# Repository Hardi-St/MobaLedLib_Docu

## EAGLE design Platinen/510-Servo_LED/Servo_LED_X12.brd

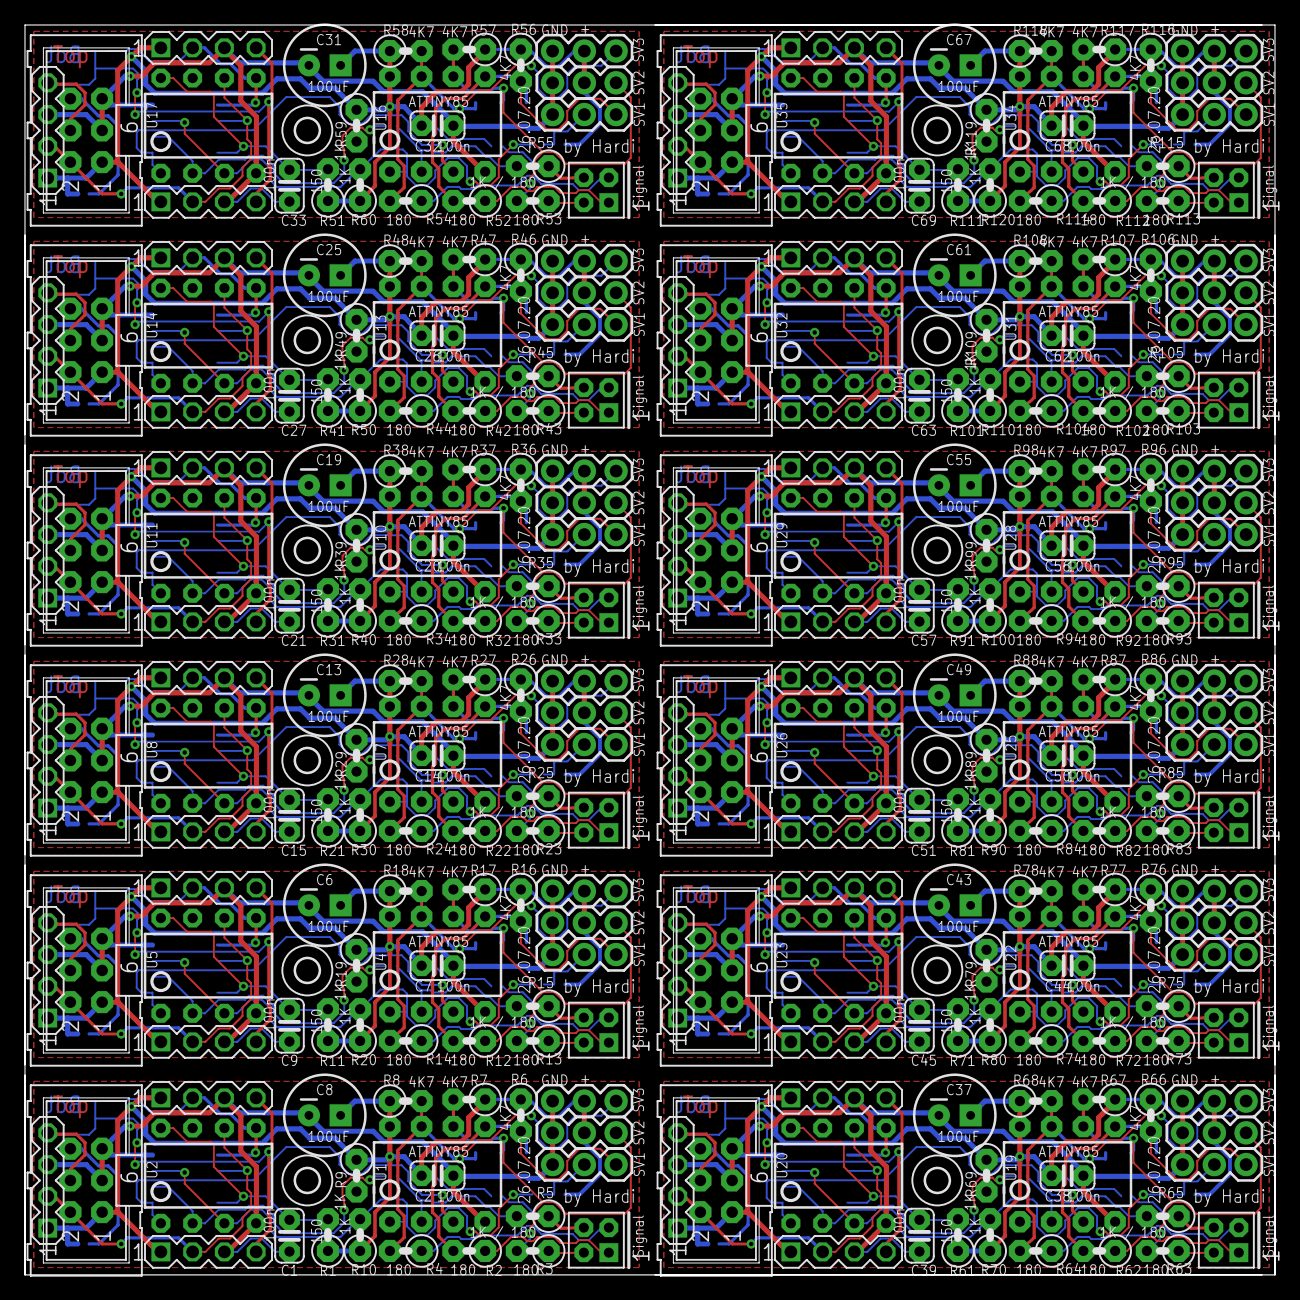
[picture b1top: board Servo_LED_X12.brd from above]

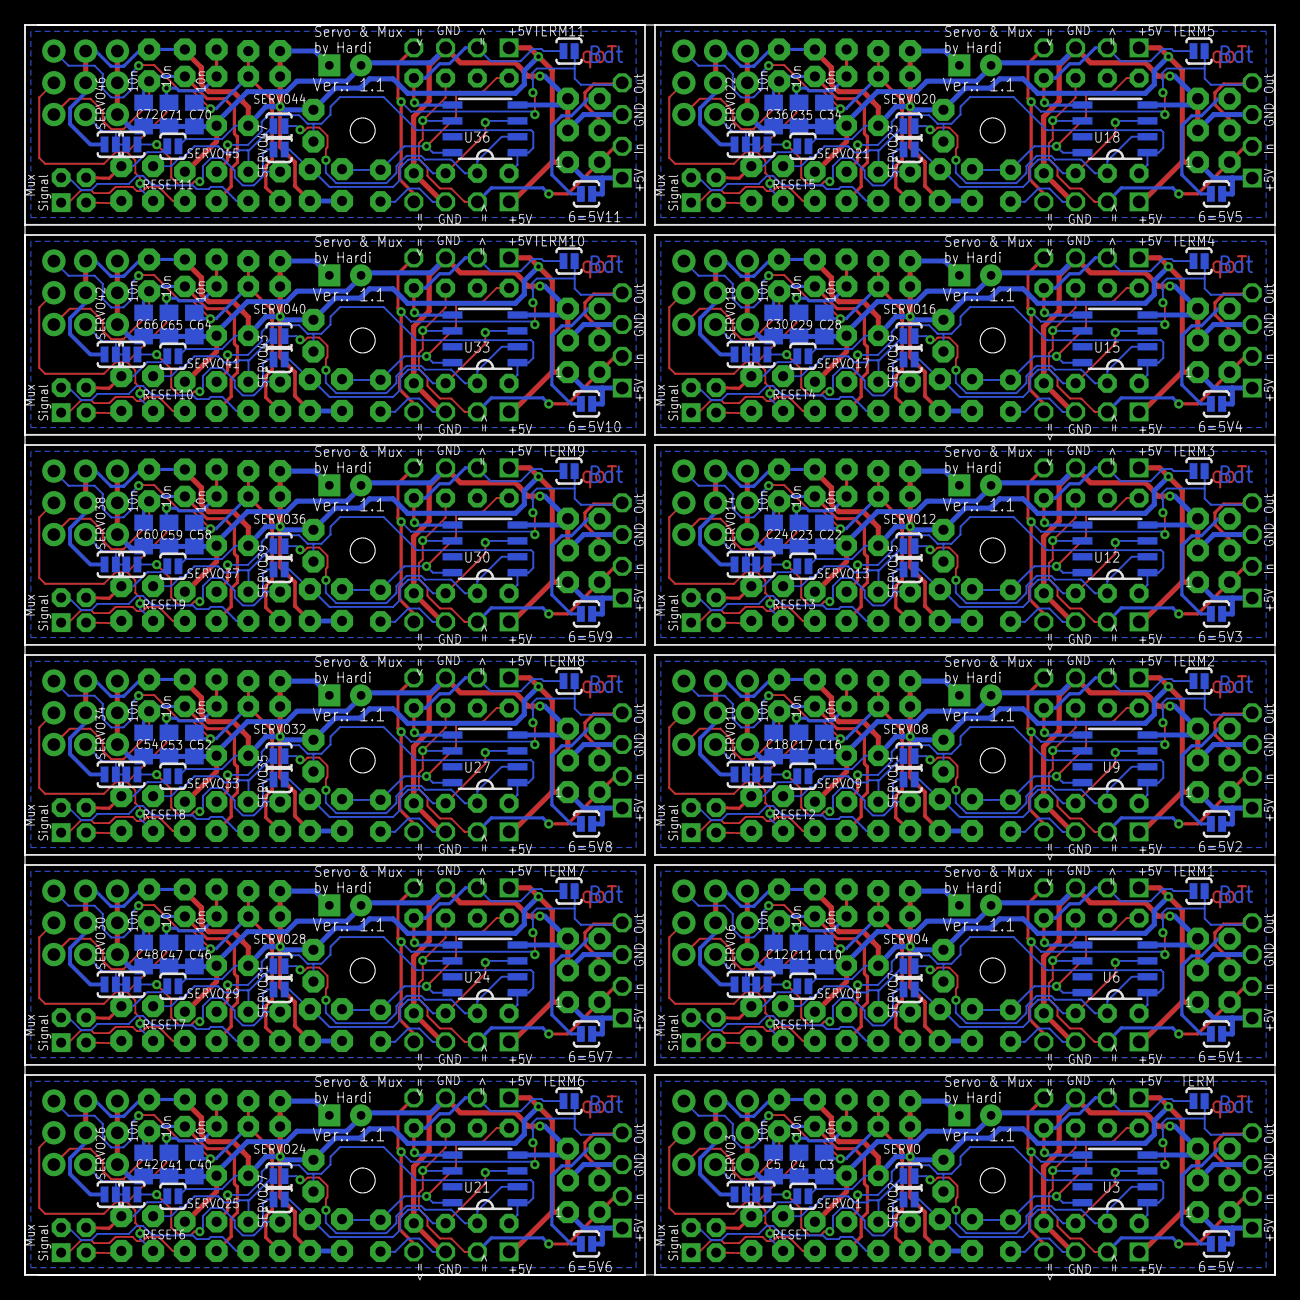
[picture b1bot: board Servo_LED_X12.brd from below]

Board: 2 copper layers, 100.0 x 100.0 mm, 420 parts (132 on the bottom side), 240 nets.

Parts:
6=5V, 6=5V1, 6=5V2, 6=5V3, 6=5V4, 6=5V5, 6=5V6, 6=5V7, 6=5V8, 6=5V9, 6=5V10, 6=5V11: SOLDERJUMPERNO; SJ_2S-NO
C1, C2, C7, C9, C14, C15, C20, C21, C26, C27, C32, C33, C38, C39, C44, C45, C50, C51, C56, C57, C62, C63, C68, C69: 100n; C025-024X044
C3, C4, C5, C10, C11, C12, C16, C17, C18, C22, C23, C24, C28, C29, C30, C34, C35, C36, C40, C41, C42, C46, C47, C48, C52, C53, C54, C58, C59, C60, C64, C65, C66, C70, C71, C72: 10n; C0805
C6, C8, C13, C19, C25, C31, C37, C43, C49, C55, C61, C67: 100uF; SPARKFUN-CAPACITORS_CPOL-RADIAL-100UF-25V
H1, H2, H3, H4, H5, H6, H7, H8, H9, H10, H11, H12: MOUNT-HOLE2.0; 2,0
J1, J4, J7, J10, J13, J16, J19, J22, J25, J28, J31, J34: SV1; 1X03
J2, J5, J8, J11, J14, J17, J20, J23, J26, J29, J32, J35: SV2; 1X03
J3, J6, J9, J12, J15, J18, J21, J24, J27, J30, J33, J36: SV3; 1X03
O1, O2, O3, O4, O5, O6, O7, O8, O9, O10, O11, O12: ML6
R1, R11, R21, R31, R41, R51, R61, R71, R81, R91, R101, R111: 150; RCL_0207/2V
R2, R3, R4, R12, R13, R14, R22, R23, R24, R32, R33, R34, R42, R43, R44, R52, R53, R54, R62, R63, R64, R72, R73, R74, R82, R83, R84, R92, R93, R94, R102, R103, R104, R112, R113, R114: 180; RCL_0207/2V
R5, R15, R25, R35, R45, R55, R65, R75, R85, R95, R105, R115: 1K / 180; RCL_0207/2V
R6, R7, R8, R16, R17, R18, R26, R27, R28, R36, R37, R38, R46, R47, R48, R56, R57, R58, R66, R67, R68, R76, R77, R78, R86, R87, R88, R96, R97, R98, R106, R107, R108, R116, R117, R118: 4K7; RCL_0207/2V
R9, R10, R19, R20, R29, R30, R39, R40, R49, R50, R59, R60, R69, R70, R79, R80, R89, R90, R99, R100, R109, R110, R119, R120: 1K; RCL_0207/2V
RESET, RESET1, RESET2, RESET3, RESET4, RESET5, RESET6, RESET7, RESET8, RESET9, RESET10, RESET11: SOLDERJUMPERNO; SJ_2S-NO
SERVO, SERVO1, SERVO2, SERVO3, SERVO4, SERVO5, SERVO6, SERVO7, SERVO8, SERVO9, SERVO10, SERVO11, SERVO12, SERVO13, SERVO14, SERVO15, SERVO16, SERVO17, SERVO18, SERVO19, SERVO20, SERVO21, SERVO22, SERVO23, SERVO24, SERVO25, SERVO26, SERVO27, SERVO28, SERVO29, SERVO30, SERVO31, SERVO32, SERVO33, SERVO34, SERVO35, SERVO36, SERVO37, SERVO38, SERVO39, SERVO40, SERVO41, SERVO42, SERVO43, SERVO44, SERVO45, SERVO46, SERVO47: SOLDERJUMPERNO; SJ_2S-NO
SV1, SV8, SV12, SV16, SV20, SV24, SV28, SV32, SV36, SV40, SV44, SV48: MUX-SIGNAL
SV2, SV3, SV4, SV5, SV6, SV7, SV9, SV10, SV11, SV13, SV14, SV15, SV17, SV18, SV19, SV21, SV22, SV23, SV25, SV26, SV27, SV29, SV30, SV31, SV33, SV34, SV35, SV37, SV38, SV39, SV41, SV42, SV43, SV45, SV46, SV47: MA04-1
TERM, TERM1, TERM2, TERM3, TERM4, TERM5, TERM6, TERM7, TERM8, TERM9, TERM10, TERM11: SOLDERJUMPERNO; SJ_2S-NO
U1, U4, U7, U10, U13, U16, U19, U22, U25, U28, U31, U34: ATTINY85; DIP08
U2, U5, U8, U11, U14, U17, U20, U23, U26, U29, U32, U35: TINY45-20-DIP; S3PO_MODUL_WS2811_SOUND_MP3-TF-16P_WS2811_AND_ATTINY_WS2811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
U3, U6, U9, U12, U15, U18, U21, U24, U27, U30, U33, U36: WS2811 SOT-8; SOP8

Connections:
+5V: 6=5V.2, C2.1, C8.1, J2.2, J3.2, O1.1, R1.1, R6.1, R7.1, R8.1, R9.1, R10.1, SERVO1.2, SERVO3.2, SV3.1, SV4.1, SV5.1, U1.8
+5V1: 6=5V1.2, C6.1, C7.1, J5.2, J6.2, O2.1, R11.1, R16.1, R17.1, R18.1, R19.1, R20.1, SERVO5.2, SERVO6.2, SV2.1, SV6.1, SV7.1, U4.8
+5V2: 6=5V2.2, C13.1, C14.1, J8.2, J9.2, O3.1, R21.1, R26.1, R27.1, R28.1, R29.1, R30.1, SERVO9.2, SERVO10.2, SV9.1, SV10.1, SV11.1, U7.8
+5V3: 6=5V3.2, C19.1, C20.1, J11.2, J12.2, O4.1, R31.1, R36.1, R37.1, R38.1, R39.1, R40.1, SERVO13.2, SERVO14.2, SV13.1, SV14.1, SV15.1, U10.8
+5V4: 6=5V4.2, C25.1, C26.1, J14.2, J15.2, O5.1, R41.1, R46.1, R47.1, R48.1, R49.1, R50.1, SERVO17.2, SERVO18.2, SV17.1, SV18.1, SV19.1, U13.8
+5V5: 6=5V5.2, C31.1, C32.1, J17.2, J18.2, O6.1, R51.1, R56.1, R57.1, R58.1, R59.1, R60.1, SERVO21.2, SERVO22.2, SV21.1, SV22.1, SV23.1, U16.8
+5V6: 6=5V6.2, C37.1, C38.1, J20.2, J21.2, O7.1, R61.1, R66.1, R67.1, R68.1, R69.1, R70.1, SERVO25.2, SERVO26.2, SV25.1, SV26.1, SV27.1, U19.8
+5V7: 6=5V7.2, C43.1, C44.1, J23.2, J24.2, O8.1, R71.1, R76.1, R77.1, R78.1, R79.1, R80.1, SERVO29.2, SERVO30.2, SV29.1, SV30.1, SV31.1, U22.8
+5V8: 6=5V8.2, C49.1, C50.1, J26.2, J27.2, O9.1, R81.1, R86.1, R87.1, R88.1, R89.1, R90.1, SERVO33.2, SERVO34.2, SV33.1, SV34.1, SV35.1, U25.8
+5V9: 6=5V9.2, C55.1, C56.1, J29.2, J30.2, O10.1, R91.1, R96.1, R97.1, R98.1, R99.1, R100.1, SERVO37.2, SERVO38.2, SV37.1, SV38.1, SV39.1, U28.8
+5V10: 6=5V10.2, C61.1, C62.1, J32.2, J33.2, O11.1, R101.1, R106.1, R107.1, R108.1, R109.1, R110.1, SERVO41.2, SERVO42.2, SV41.1, SV42.1, SV43.1, U31.8
+5V11: 6=5V11.2, C67.1, C68.1, J35.2, J36.2, O12.1, R111.1, R116.1, R117.1, R118.1, R119.1, R120.1, SERVO45.2, SERVO46.2, SV45.1, SV46.1, SV47.1, U34.8
GND: C1.2, C2.2, C3.2, C4.2, C5.2, C8.2, J1.3, J2.3, J3.3, O1.3, O1.5, SV3.3, SV4.3, SV5.3, U1.4, U2.4, U3.4
GND1: C6.2, C7.2, C9.2, C10.2, C11.2, C12.2, J4.3, J5.3, J6.3, O2.3, O2.5, SV2.3, SV6.3, SV7.3, U4.4, U5.4, U6.4
GND2: C13.2, C14.2, C15.2, C16.2, C17.2, C18.2, J7.3, J8.3, J9.3, O3.3, O3.5, SV9.3, SV10.3, SV11.3, U7.4, U8.4, U9.4
GND3: C19.2, C20.2, C21.2, C22.2, C23.2, C24.2, J10.3, J11.3, J12.3, O4.3, O4.5, SV13.3, SV14.3, SV15.3, U10.4, U11.4, U12.4
GND4: C25.2, C26.2, C27.2, C28.2, C29.2, C30.2, J13.3, J14.3, J15.3, O5.3, O5.5, SV17.3, SV18.3, SV19.3, U13.4, U14.4, U15.4
GND5: C31.2, C32.2, C33.2, C34.2, C35.2, C36.2, J16.3, J17.3, J18.3, O6.3, O6.5, SV21.3, SV22.3, SV23.3, U16.4, U17.4, U18.4
GND6: C37.2, C38.2, C39.2, C40.2, C41.2, C42.2, J19.3, J20.3, J21.3, O7.3, O7.5, SV25.3, SV26.3, SV27.3, U19.4, U20.4, U21.4
GND7: C43.2, C44.2, C45.2, C46.2, C47.2, C48.2, J22.3, J23.3, J24.3, O8.3, O8.5, SV29.3, SV30.3, SV31.3, U22.4, U23.4, U24.4
GND8: C49.2, C50.2, C51.2, C52.2, C53.2, C54.2, J25.3, J26.3, J27.3, O9.3, O9.5, SV33.3, SV34.3, SV35.3, U25.4, U26.4, U27.4
GND9: C55.2, C56.2, C57.2, C58.2, C59.2, C60.2, J28.3, J29.3, J30.3, O10.3, O10.5, SV37.3, SV38.3, SV39.3, U28.4, U29.4, U30.4
GND10: C61.2, C62.2, C63.2, C64.2, C65.2, C66.2, J31.3, J32.3, J33.3, O11.3, O11.5, SV41.3, SV42.3, SV43.3, U31.4, U32.4, U33.4
GND11: C67.2, C68.2, C69.2, C70.2, C71.2, C72.2, J34.3, J35.3, J36.3, O12.3, O12.5, SV45.3, SV46.3, SV47.3, U34.4, U35.4, U36.4
unnamed: O1.2, SV4.2, SV5.2, U2.6, U3.6
unnamed: SV3.2, TERM.2, U2.5, U3.5
unnamed: O1.4, SV3.4, SV4.4, SV5.4, TERM.1
unnamed: C1.1, R1.2, U2.8, U3.8
unnamed: R2.1, SV1.1
unnamed: 6=5V.1, O1.6
unnamed: R9.2, U1.3, U2.1, U3.1
unnamed: R5.2, SERVO.2, U1.2
unnamed: C4.1, J2.1, R3.2, R7.2, U1.6
unnamed: R4.1, SV1.3
unnamed: R3.1, SV1.2
unnamed: R5.1, SERVO1.1, SV1.4
unnamed: SERVO.1, U2.2, U3.2
unnamed: C3.1, J3.1, R4.2, R8.2, U1.7
unnamed: RESET.1, SERVO2.2, U1.1
unnamed: C5.1, J1.1, R2.2, R6.2, U1.5
unnamed: J1.2, RESET.2, SERVO3.1
unnamed: R10.2, SERVO2.1, U2.3, U3.3
unnamed: O2.2, SV6.2, SV7.2, U5.6, U6.6
unnamed: SV2.2, TERM1.2, U5.5, U6.5
unnamed: O2.4, SV2.4, SV6.4, SV7.4, TERM1.1
unnamed: C9.1, R11.2, U5.8, U6.8
unnamed: R19.2, U4.3, U5.1, U6.1
unnamed: C11.1, J5.1, R13.2, R17.2, U4.6
unnamed: C10.1, J6.1, R14.2, R18.2, U4.7
unnamed: C12.1, J4.1, R12.2, R16.2, U4.5
unnamed: RESET1.1, SERVO7.2, U4.1
unnamed: R12.1, SV8.1
unnamed: R14.1, SV8.3
unnamed: R13.1, SV8.2
unnamed: R15.1, SERVO5.1, SV8.4
unnamed: R15.2, SERVO4.2, U4.2
unnamed: SERVO4.1, U5.2, U6.2
unnamed: 6=5V1.1, O2.6
unnamed: J4.2, RESET1.2, SERVO6.1
unnamed: R20.2, SERVO7.1, U5.3, U6.3
unnamed: O3.2, SV10.2, SV11.2, U8.6, U9.6
unnamed: SV9.2, TERM2.2, U8.5, U9.5
unnamed: O3.4, SV9.4, SV10.4, SV11.4, TERM2.1
unnamed: C15.1, R21.2, U8.8, U9.8
unnamed: R29.2, U7.3, U8.1, U9.1
unnamed: C17.1, J8.1, R23.2, R27.2, U7.6
unnamed: C16.1, J9.1, R24.2, R28.2, U7.7
unnamed: C18.1, J7.1, R22.2, R26.2, U7.5
unnamed: RESET2.1, SERVO11.2, U7.1
unnamed: R22.1, SV12.1
unnamed: R24.1, SV12.3
unnamed: R23.1, SV12.2
unnamed: R25.1, SERVO9.1, SV12.4
unnamed: R25.2, SERVO8.2, U7.2
unnamed: SERVO8.1, U8.2, U9.2
unnamed: 6=5V2.1, O3.6
unnamed: J7.2, RESET2.2, SERVO10.1
unnamed: R30.2, SERVO11.1, U8.3, U9.3
unnamed: O4.2, SV14.2, SV15.2, U11.6, U12.6
unnamed: SV13.2, TERM3.2, U11.5, U12.5
unnamed: O4.4, SV13.4, SV14.4, SV15.4, TERM3.1
unnamed: C21.1, R31.2, U11.8, U12.8
unnamed: R39.2, U10.3, U11.1, U12.1
unnamed: C23.1, J11.1, R33.2, R37.2, U10.6
unnamed: C22.1, J12.1, R34.2, R38.2, U10.7
unnamed: C24.1, J10.1, R32.2, R36.2, U10.5
unnamed: RESET3.1, SERVO15.2, U10.1
unnamed: R32.1, SV16.1
unnamed: R34.1, SV16.3
unnamed: R33.1, SV16.2
unnamed: R35.1, SERVO13.1, SV16.4
unnamed: R35.2, SERVO12.2, U10.2
unnamed: SERVO12.1, U11.2, U12.2
unnamed: 6=5V3.1, O4.6
unnamed: J10.2, RESET3.2, SERVO14.1
unnamed: R40.2, SERVO15.1, U11.3, U12.3
unnamed: O5.2, SV18.2, SV19.2, U14.6, U15.6
unnamed: SV17.2, TERM4.2, U14.5, U15.5
unnamed: O5.4, SV17.4, SV18.4, SV19.4, TERM4.1
unnamed: C27.1, R41.2, U14.8, U15.8
unnamed: R49.2, U13.3, U14.1, U15.1
unnamed: C29.1, J14.1, R43.2, R47.2, U13.6
unnamed: C28.1, J15.1, R44.2, R48.2, U13.7
unnamed: C30.1, J13.1, R42.2, R46.2, U13.5
unnamed: RESET4.1, SERVO19.2, U13.1
unnamed: R42.1, SV20.1
unnamed: R44.1, SV20.3
unnamed: R43.1, SV20.2
unnamed: R45.1, SERVO17.1, SV20.4
unnamed: R45.2, SERVO16.2, U13.2
unnamed: SERVO16.1, U14.2, U15.2
unnamed: 6=5V4.1, O5.6
unnamed: J13.2, RESET4.2, SERVO18.1
unnamed: R50.2, SERVO19.1, U14.3, U15.3
unnamed: O6.2, SV22.2, SV23.2, U17.6, U18.6
unnamed: SV21.2, TERM5.2, U17.5, U18.5
unnamed: O6.4, SV21.4, SV22.4, SV23.4, TERM5.1
unnamed: C33.1, R51.2, U17.8, U18.8
unnamed: R59.2, U16.3, U17.1, U18.1
unnamed: C35.1, J17.1, R53.2, R57.2, U16.6
unnamed: C34.1, J18.1, R54.2, R58.2, U16.7
unnamed: C36.1, J16.1, R52.2, R56.2, U16.5
unnamed: RESET5.1, SERVO23.2, U16.1
unnamed: R52.1, SV24.1
unnamed: R54.1, SV24.3
unnamed: R53.1, SV24.2
unnamed: R55.1, SERVO21.1, SV24.4
unnamed: R55.2, SERVO20.2, U16.2
unnamed: SERVO20.1, U17.2, U18.2
unnamed: 6=5V5.1, O6.6
unnamed: J16.2, RESET5.2, SERVO22.1
unnamed: R60.2, SERVO23.1, U17.3, U18.3
unnamed: O7.2, SV26.2, SV27.2, U20.6, U21.6
unnamed: SV25.2, TERM6.2, U20.5, U21.5
unnamed: O7.4, SV25.4, SV26.4, SV27.4, TERM6.1
unnamed: C39.1, R61.2, U20.8, U21.8
unnamed: R69.2, U19.3, U20.1, U21.1
unnamed: C41.1, J20.1, R63.2, R67.2, U19.6
unnamed: C40.1, J21.1, R64.2, R68.2, U19.7
unnamed: C42.1, J19.1, R62.2, R66.2, U19.5
unnamed: RESET6.1, SERVO27.2, U19.1
unnamed: R62.1, SV28.1
unnamed: R64.1, SV28.3
unnamed: R63.1, SV28.2
unnamed: R65.1, SERVO25.1, SV28.4
unnamed: R65.2, SERVO24.2, U19.2
unnamed: SERVO24.1, U20.2, U21.2
unnamed: 6=5V6.1, O7.6
unnamed: J19.2, RESET6.2, SERVO26.1
unnamed: R70.2, SERVO27.1, U20.3, U21.3
unnamed: O8.2, SV30.2, SV31.2, U23.6, U24.6
unnamed: SV29.2, TERM7.2, U23.5, U24.5
unnamed: O8.4, SV29.4, SV30.4, SV31.4, TERM7.1
unnamed: C45.1, R71.2, U23.8, U24.8
unnamed: R79.2, U22.3, U23.1, U24.1
unnamed: C47.1, J23.1, R73.2, R77.2, U22.6
unnamed: C46.1, J24.1, R74.2, R78.2, U22.7
unnamed: C48.1, J22.1, R72.2, R76.2, U22.5
unnamed: RESET7.1, SERVO31.2, U22.1
unnamed: R72.1, SV32.1
unnamed: R74.1, SV32.3
unnamed: R73.1, SV32.2
unnamed: R75.1, SERVO29.1, SV32.4
unnamed: R75.2, SERVO28.2, U22.2
unnamed: SERVO28.1, U23.2, U24.2
unnamed: 6=5V7.1, O8.6
unnamed: J22.2, RESET7.2, SERVO30.1
unnamed: R80.2, SERVO31.1, U23.3, U24.3
unnamed: O9.2, SV34.2, SV35.2, U26.6, U27.6
unnamed: SV33.2, TERM8.2, U26.5, U27.5
unnamed: O9.4, SV33.4, SV34.4, SV35.4, TERM8.1
unnamed: C51.1, R81.2, U26.8, U27.8
unnamed: R89.2, U25.3, U26.1, U27.1
unnamed: C53.1, J26.1, R83.2, R87.2, U25.6
unnamed: C52.1, J27.1, R84.2, R88.2, U25.7
unnamed: C54.1, J25.1, R82.2, R86.2, U25.5
unnamed: RESET8.1, SERVO35.2, U25.1
unnamed: R82.1, SV36.1
unnamed: R84.1, SV36.3
unnamed: R83.1, SV36.2
unnamed: R85.1, SERVO33.1, SV36.4
unnamed: R85.2, SERVO32.2, U25.2
unnamed: SERVO32.1, U26.2, U27.2
unnamed: 6=5V8.1, O9.6
unnamed: J25.2, RESET8.2, SERVO34.1
unnamed: R90.2, SERVO35.1, U26.3, U27.3
unnamed: O10.2, SV38.2, SV39.2, U29.6, U30.6
unnamed: SV37.2, TERM9.2, U29.5, U30.5
unnamed: O10.4, SV37.4, SV38.4, SV39.4, TERM9.1
unnamed: C57.1, R91.2, U29.8, U30.8
unnamed: R99.2, U28.3, U29.1, U30.1
unnamed: C59.1, J29.1, R93.2, R97.2, U28.6
unnamed: C58.1, J30.1, R94.2, R98.2, U28.7
unnamed: C60.1, J28.1, R92.2, R96.2, U28.5
unnamed: RESET9.1, SERVO39.2, U28.1
unnamed: R92.1, SV40.1
unnamed: R94.1, SV40.3
unnamed: R93.1, SV40.2
unnamed: R95.1, SERVO37.1, SV40.4
unnamed: R95.2, SERVO36.2, U28.2
unnamed: SERVO36.1, U29.2, U30.2
unnamed: 6=5V9.1, O10.6
unnamed: J28.2, RESET9.2, SERVO38.1
unnamed: R100.2, SERVO39.1, U29.3, U30.3
unnamed: O11.2, SV42.2, SV43.2, U32.6, U33.6
unnamed: SV41.2, TERM10.2, U32.5, U33.5
unnamed: O11.4, SV41.4, SV42.4, SV43.4, TERM10.1
unnamed: C63.1, R101.2, U32.8, U33.8
unnamed: R109.2, U31.3, U32.1, U33.1
unnamed: C65.1, J32.1, R103.2, R107.2, U31.6
unnamed: C64.1, J33.1, R104.2, R108.2, U31.7
unnamed: C66.1, J31.1, R102.2, R106.2, U31.5
unnamed: RESET10.1, SERVO43.2, U31.1
unnamed: R102.1, SV44.1
unnamed: R104.1, SV44.3
unnamed: R103.1, SV44.2
unnamed: R105.1, SERVO41.1, SV44.4
unnamed: R105.2, SERVO40.2, U31.2
unnamed: SERVO40.1, U32.2, U33.2
unnamed: 6=5V10.1, O11.6
unnamed: J31.2, RESET10.2, SERVO42.1
unnamed: R110.2, SERVO43.1, U32.3, U33.3
unnamed: O12.2, SV46.2, SV47.2, U35.6, U36.6
unnamed: SV45.2, TERM11.2, U35.5, U36.5
unnamed: O12.4, SV45.4, SV46.4, SV47.4, TERM11.1
unnamed: C69.1, R111.2, U35.8, U36.8
unnamed: R119.2, U34.3, U35.1, U36.1
unnamed: C71.1, J35.1, R113.2, R117.2, U34.6
unnamed: C70.1, J36.1, R114.2, R118.2, U34.7
unnamed: C72.1, J34.1, R112.2, R116.2, U34.5
unnamed: RESET11.1, SERVO47.2, U34.1
unnamed: R112.1, SV48.1
unnamed: R114.1, SV48.3
unnamed: R113.1, SV48.2
unnamed: R115.1, SERVO45.1, SV48.4
unnamed: R115.2, SERVO44.2, U34.2
unnamed: SERVO44.1, U35.2, U36.2
unnamed: 6=5V11.1, O12.6
unnamed: J34.2, RESET11.2, SERVO46.1
unnamed: R120.2, SERVO47.1, U35.3, U36.3

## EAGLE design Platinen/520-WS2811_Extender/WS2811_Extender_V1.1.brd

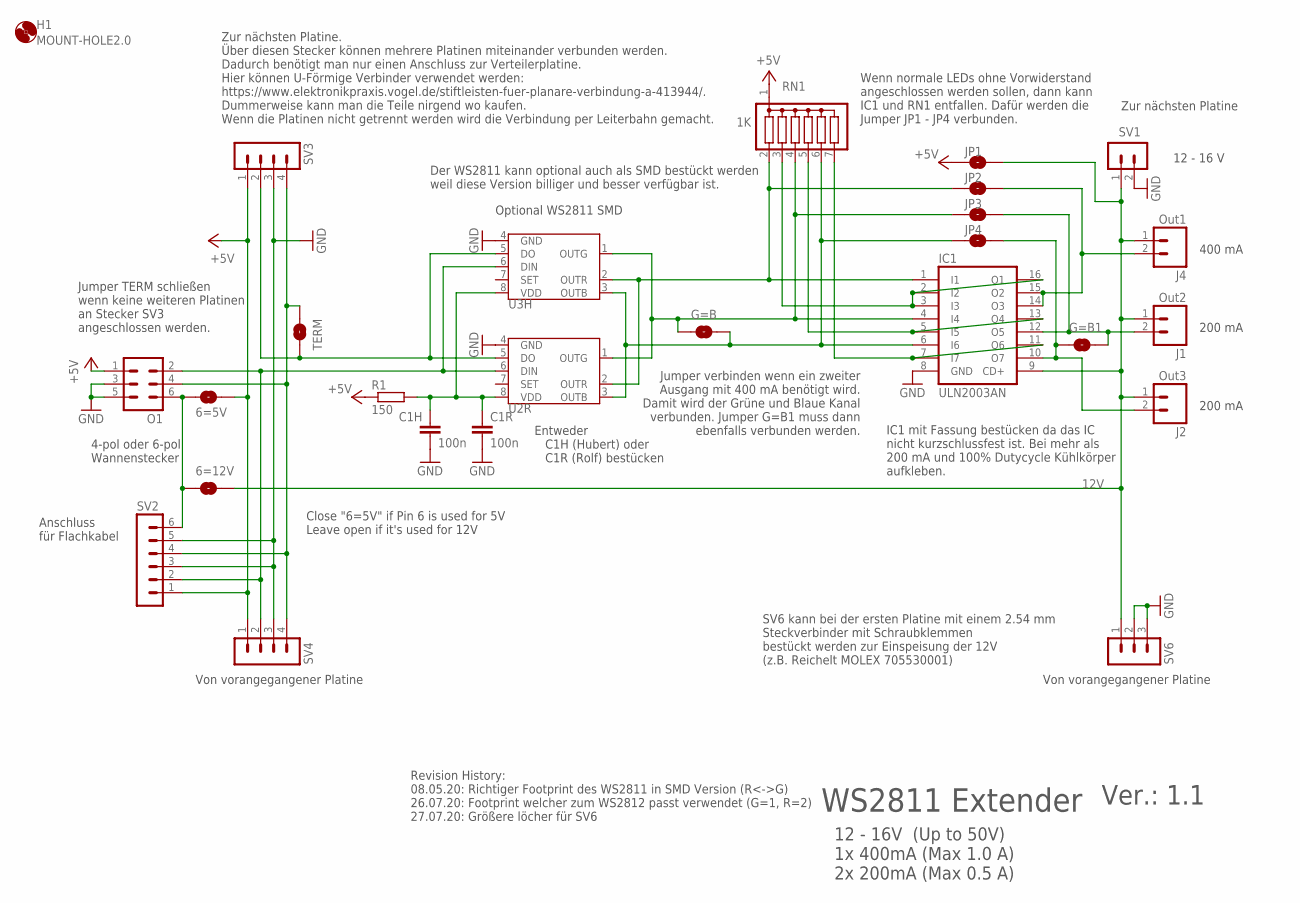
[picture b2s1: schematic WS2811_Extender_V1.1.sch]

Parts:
6=5V, 6=12V: SOLDERJUMPERNO; SJ_2S-NO
C1H: 100n; C1206
C1R: 100n; C025-024X044
G=B, G=B1: SOLDERJUMPERNO; SJ_2S-NO
H1: MOUNT-HOLE2.0; 2,0
IC1: ULN2003AN; DIL16
J1: Out2; 1X02
J2: Out3; 1X02
J4: Out1; 1X02
JP1, JP2, JP3, JP4: SOLDERJUMPERNO; SJ_2S-NO
O1: ML6
R1: 150; RCL_0207/2V
RN1: 1K; SIL7
SV1: MA02-1
SV2: MA06-1
SV3, SV4: MA04-1
SV6: MA03-1
TERM: SOLDERJUMPERNO; SJ_2S-NO
U2R: TINY45-20-DIP; S3PO_MODUL_WS2811_SOUND_MP3-TF-16P_WS2811_AND_ATTINY_WS2811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
U3H: WS2811 SOT-8; SOP8

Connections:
12V: 6=12V.2, IC1.9 (CD+), J1.1, J2.1, J4.1, JP1.2, SV1.1, SV6.1
+5V: 6=5V.2, JP1.1, O1.1, R1.1, RN1.1, SV2.1, SV3.1, SV4.1
GND: C1H.2, C1R.2, IC1.8 (GND), O1.3, O1.5, SV1.2, SV2.3, SV2.5, SV3.3, SV4.3, SV6.2, SV6.3, U2R.4 (GND), U3H.4 (GND)
unnamed: O1.2, SV2.2, SV4.2, U2R.6 (DIN), U3H.6 (DIN)
unnamed: SV3.2, TERM.2, U2R.5 (DO), U3H.5 (DO)
unnamed: O1.4, SV2.4, SV3.4, SV4.4, TERM.1
unnamed: C1H.1, C1R.1, R1.2, U2R.8 (VDD), U3H.8 (VDD)
unnamed: IC1.1 (I1), JP2.1, RN1.2, U2R.2 (OUTR), U3H.2 (OUTR)
unnamed: 6=5V.1, 6=12V.1, O1.6, SV2.6
unnamed: G=B.2, IC1.6 (I6), JP4.1, RN1.6, U2R.3 (OUTB), U3H.3 (OUTB)
unnamed: IC1.2 (I2), IC1.3 (I3), IC1.16 (O1), RN1.3
unnamed: IC1.5 (I5), IC1.13 (O4), RN1.5
unnamed: IC1.7 (I7), IC1.11 (O6), RN1.7
unnamed: G=B.1, IC1.4 (I4), JP3.1, RN1.4, U2R.1 (OUTG), U3H.1 (OUTG)
O1: IC1.14 (O3), IC1.15 (O2), J4.2, JP2.2
O2: G=B1.2, IC1.12 (O5), J1.2, JP3.2
O3: G=B1.1, IC1.10 (O7), J2.2, JP4.2

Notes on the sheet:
Anschluss für Flachkabel
4-pol oder 6-pol Wannenstecker
Close "6=5V" if Pin 6 is used for 5V Leave open if it's used for 12V
Optional WS2811 SMD
Zur nächsten Platine. Über diesen Stecker können mehrere Platinen miteinander verbunden werden. Dadurch benötigt man nur einen Anschluss zur Verteilerplatine. Hier können U-Förmige Verbinder verwendet werden: https://www.elektronikpraxis.vogel.de/stiftleisten-fuer-planare-verbindung-a-413944/. Dumm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
Von vorangegangener Platine
Der WS2811 kann optional auch als SMD bestückt werden weil diese Version billiger und besser verfügbar ist.
400 mA
200 mA
12 - 16 V
WS2811 Extender
12 - 16V (Up to 50V) 1x 400mA (Max 1.0 A) 2x 200mA (Max 0.5 A)
Ver.: 1.1
Entweder C1H (Hubert) oder C1R (Rolf) bestücken
Jumper verbinden wenn ein zweiter Ausgang mit 400 mA benötigt wird. Damit wird der Grüne und Blaue Kanal verbunden. Jumper G=B1 muss dann ebenfalls verbunden werden.
Jumper TERM schließen wenn keine weiteren Platinen an Stecker SV3 angeschlossen werden.
SV6 kann bei der ersten Platine mit einem 2.54 mm Steckverbinder mit Schraubklemmen bestückt werden zur Einspeisung der 12V (z.B. Reichelt MOLEX 705530001)
Zur nächsten Platine
IC1 mit Fassung bestücken da das IC nicht kurzschlussfest ist. Bei mehr als 200 mA und 100% Dutycycle Kühlkörper aufkleben.
Wenn normale LEDs ohne Vorwiderstand angeschlossen werden sollen, dann kann IC1 und RN1 entfallen. Dafür werden die Jumper JP1 - JP4 verbunden.
Revision History: 08.05.20: Richtiger Footprint des WS2811 in SMD Version (R<->G) 26.07.20: Footprint welcher zum WS2812 passt verwendet (G=1, R=2) 27.07.20: Größere löcher für SV6

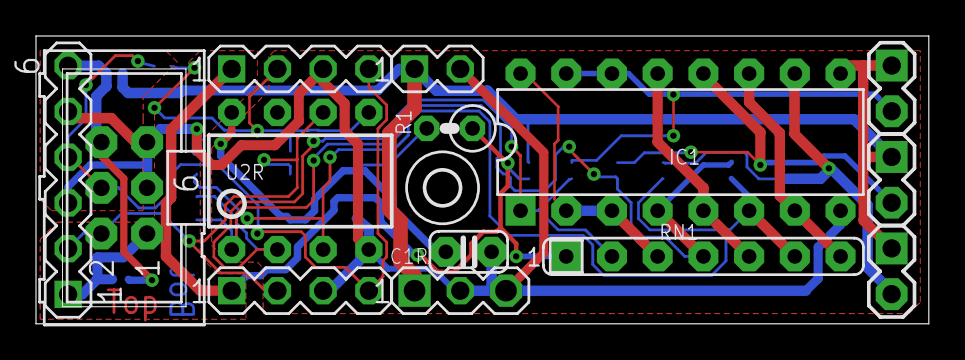
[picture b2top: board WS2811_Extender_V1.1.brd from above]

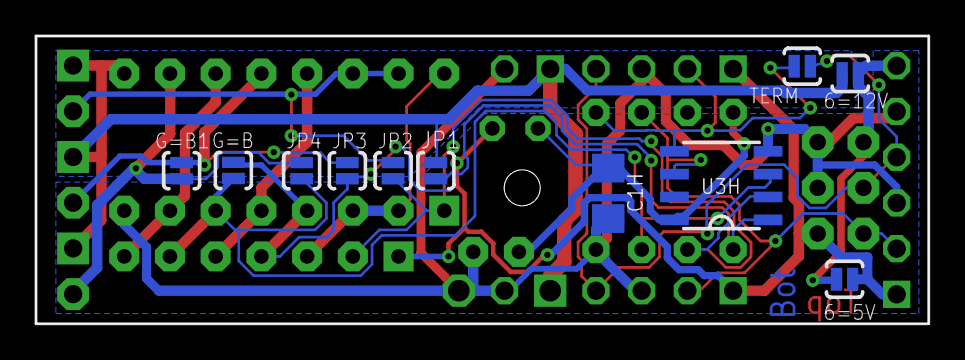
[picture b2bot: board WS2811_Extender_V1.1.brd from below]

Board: 2 copper layers, 49.6 x 16.0 mm, 26 parts (11 on the bottom side), 17 nets.

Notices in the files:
parts and their libraries:
SparkFun-DigitalIC: Licensing: Creative Commons ShareAlike 4.0 International - https://creativecommons.org/licenses/by-sa/4.0
